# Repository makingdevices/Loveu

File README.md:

<!-- Improved compatibility of back to top link: See: https://github.com/othneildrew/Best-README-Template/pull/73 -->

<!--
*** Thanks for checking out the Best-README-Template. If you have a suggestion
*** that would make this better, please fork the repo and create a pull request
*** or simply open an issue with the tag "enhancement".
*** Don't forget to give the project a star!
*** Thanks again! Now go create something AMAZING! :D
-->

<!-- PROJECT SHIELDS -->
<!--
*** I'm using markdown "reference style" links for readability.
*** Reference links are enclosed in brackets [ ] instead of parentheses ( ).
*** See the bottom of this document for the declaration of the reference variables
*** for contributors-url, forks-url, etc. This is an optional, concise syntax you may use.
*** https://www.markdownguide.org/basic-syntax/#reference-style-links
-->
[![Instagram][ig-shield]][ig-url]
[![PCBWAY][sponsor-shield]][sponsor-url]
[![Stargazers][stars-shield]][stars-url]
[![Issues][issues-shield]][issues-url]
[![LinkedIn][linkedin-shield]][linkedin-url]

<!-- PROJECT LOGO -->
<br />
<div align="center">

<h3 align="center">Making Devices</h3>

  <p align="center">
    Open Source projects where we struggle with engineering, electronics, coding and who knows what else... In this case, Loveu is a heart-shaped PCB for saint Valentine
  </p>
</div>

<!-- TABLE OF CONTENTS -->
<details>
  <summary>Table of Contents</summary>
  <ol>
    <li>
      <a href="#about-the-project">About The Project</a>
      <ul>
        <li><a href="#built-with">Built With</a></li>
      </ul>
    </li>
    <li>
      <a href="#Build-one">Build one</a>
      <ul>
      </ul>
    </li>
    <li><a href="#usage">Usage</a></li>
    <li><a href="#roadmap">Roadmap</a></li>
    <li><a href="#license">License</a></li>
    <li><a href="#contact">Contact</a></li>
    <li><a href="#Sponsor">Sponsor</a></li>
  </ol>
</details>

<!-- ABOUT THE PROJECT -->
## About The Project

[![Bytes Counter Shot][product-screenshot]](https://github.com/makingdevices/Loveu)

Heart shaped PCB that was intended to blink with the harvested power of the micro solar panels. Unfortunately, it did not work. 

This device is under development, so I do encourage you to not assembly, order any PCB or use any software from this repository until the project is finished.

<p align="right">(<a href="#readme-top">back to top</a>)</p>

### Built With

[![Kicad][kicad-shield]][kicad-url]
[![SPONSOR][sponsor-icon]][sponsor-url]

<p align="right">(<a href="#readme-top">back to top</a>)</p>

<!-- GETTING STARTED -->

## Build one
NOT RECOMMENDED AS THE DEVICE IS UNDER DEVELOPMENT

<p align="right">(<a href="#readme-top">back to top</a>)</p>

<!-- USAGE EXAMPLES -->
## Usage

Instructions of use:

- The heart blinks with the sun

<p align="right">(<a href="#readme-top">back to top</a>)</p>

<!-- ROADMAP -->
## Roadmap

- [ ] Re Design

See the [open issues](https://github.com/makingdevices/Loveu/issues) for a full list of proposed features (and known issues).

State: Project <b>UNFINISHED</b> - 08/01/2023

Priority: <b>None</b>

<p align="right">(<a href="#readme-top">back to top</a>)</p>

<!-- LICENSE -->
## License

Distributed under three licenses:
- [Hardware](/License/HW_cern_ohl_s_v2.pdf)
- [Software](/License/SW_GPLv3.0.txt)
- [Documentation](/License/Documentation_CC-BY-SA-4.0.txt)

[![GPL v3 License][license-shield]][license-url] 
<p align="right">(<a href="#readme-top">back to top</a>)</p>

<!-- CONTACT -->
## Contact

Making Devices - [@MakingDevices](https://www.instagram.com/makingdevices/)

Project Link: [https://github.com/makingdevices/Loveu](https://github.com/makingdevices/Loveu/)

Other Links: [LinkTree](https://makingdevices.com/links/)

<p align="right">(<a href="#readme-top">back to top</a>)</p>

<!-- MARKDOWN LINKS & IMAGES -->
<!-- https://www.markdownguide.org/basic-syntax/#reference-style-links -->
[contributors-shield]: https://img.shields.io/github/contributors/makingdevices/Loveu.svg?style=for-the-badge
[contributors-url]: https://github.com/makingdevices/Loveu/graphs/contributors
[forks-shield]: https://img.shields.io/github/forks/makingdevices/Loveu.svg?style=for-the-badge
[forks-url]: https://github.com/makingdevices/Loveu/network/members
[stars-shield]: https://img.shields.io/github/stars/makingdevices/Loveu.svg?style=for-the-badge
[stars-url]: https://github.com/makingdevices/Loveu/stargazers
[issues-shield]: https://img.shields.io/github/issues/makingdevices/Loveu.svg?style=for-the-badge
[issues-url]: https://github.com/makingdevices/Loveu/issues
[license-shield]: /images/license.png
[license-url]: https://github.com/makingdevices/Loveu/tree/main/License
[linkedin-shield]: https://img.shields.io/badge/-LinkedIn-black.svg?style=for-the-badge&logo=linkedin&colorB=555
[linkedin-url]: https://www.linkedin.com/company/making-devices/
[sponsor-shield]: https://img.shields.io/badge/SPONSOR-PCBWAY-black.svg?style=for-the-badge&colorB=1200
[sponsor-url]: https://www.pcbway.com/?from=makingdevices
[sponsor-screenshot]: /images/PCB_sponsor.png
[product-screenshot]: images/screenshot.jpg
[PIC]: https://img.shields.io/badge/PIC18LF45K50-000000?style=for-the-badge
[PIC-url]: http://ww1.microchip.com/downloads/en/devicedoc/40001350f.pdf
[kicad-shield]: https://img.shields.io/badge/kicad-0b03fc?style=for-the-badge&logo=kicad&logoColor=white
[kicad-url]: https://www.kicad.org/
[YT-screenshot]: images/YT_assembly.PNG
[sponsor-icon]:  https://img.shields.io/badge/-PCBWAY-black.svg?style=for-the-badge&colorB=1200
[ig-shield]: https://img.shields.io/badge/instagram-a83297?style=for-the-badge&logo=instagram&logoColor=white
[ig-url]: https://www.instagram.com/makingdevices/
[MPLAB-C]: https://img.shields.io/badge/MPLAB%20C18-DD0031?style=for-the-badge&logo=C&logoColor=white
[MPLAB-C-url]: https://www.microchip.com/en-us/development-tool/SW006011
[Svelte.dev]: https://img.shields.io/badge/Svelte-4A4A55?style=for-the-badge&logo=svelte&logoColor=FF3E00
[Svelte-url]: https://svelte.dev/
[Laravel.com]: https://img.shields.io/badge/Laravel-FF2D20?style=for-the-badge&logo=laravel&logoColor=white
[Laravel-url]: https://laravel.com
[Bootstrap.com]: https://img.shields.io/badge/Bootstrap-563D7C?style=for-the-badge&logo=bootstrap&logoColor=white
[Bootstrap-url]: https://getbootstrap.com
[JQuery.com]: https://img.shields.io/badge/jQuery-0769AD?style=for-the-badge&logo=jquery&logoColor=white
[JQuery-url]: https://jquery.com

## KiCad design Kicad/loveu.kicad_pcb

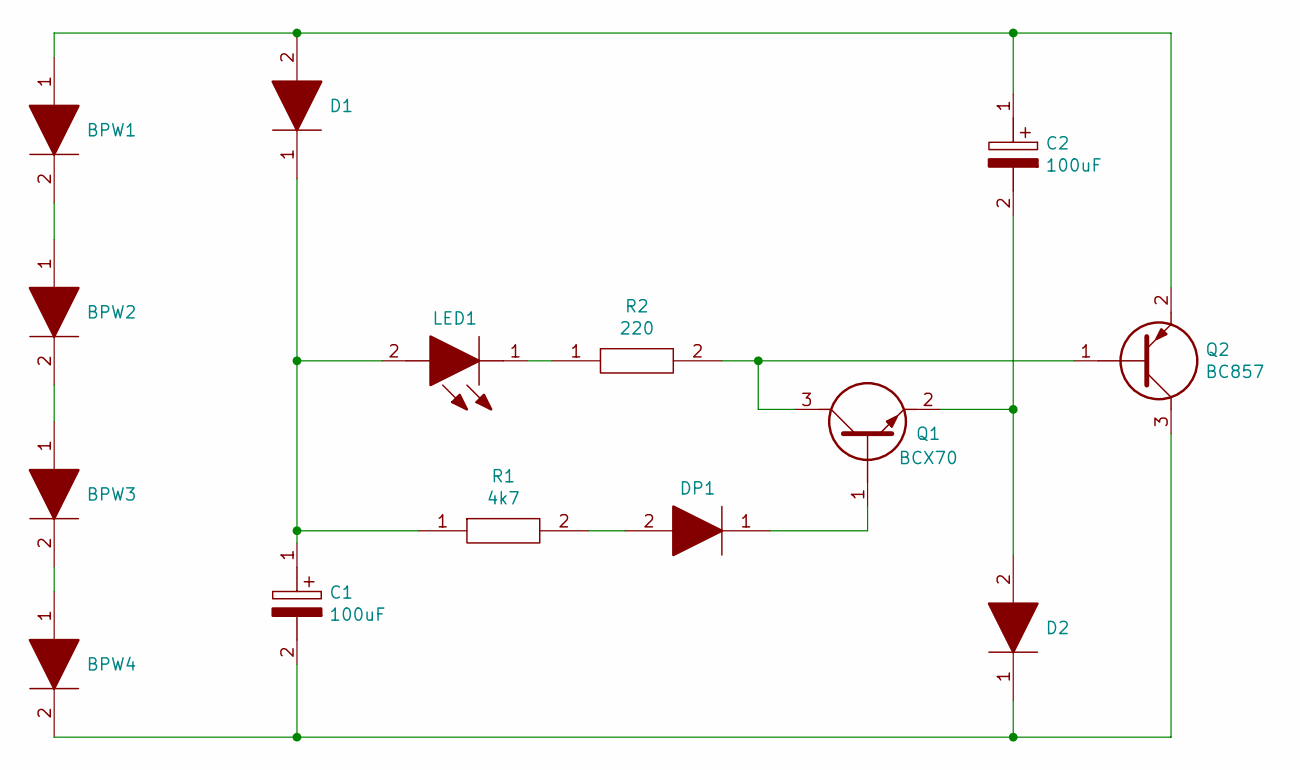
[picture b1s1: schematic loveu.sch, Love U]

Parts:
BPW1, BPW2, BPW3, BPW4: BPW_34_SR-Z; BPW34SRZ; Mouser Part Number 720-BPW34SR-Z
C1, C2: 100uF; CAPPM6032X280N; Mouser Part Number 581-TCJC107M06R100E
D1, D2: ZLLS410TA; SOD2513X120N; Manufacturer_Part_Number ZLLS410TA
DP1: BAV21WS_R1_00001; SODFL2512X90N; Mouser Part Number 241-BAV21WS_R1_00001
LED1: SML-H12V8TT86; LEDC2012X90N; Manufacturer_Part_Number SML-H12V8TT86
Q1: BCX70; SOT95P230X110-3N; Mouser Part Number 771-BCX70J235
Q2: BC857; SOT95P230X110-3N; Mouser Part Number 771-BC858B235
R1: 4k7; RESC2012X75N; Manufacturer_Part_Number ERJP6WF1303V
R2: 220; RESC2012X75N; Manufacturer_Part_Number ERJP6WF1303V

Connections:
unnamed: BPW1.1, C2.1, D1.2, Q2.2
unnamed: BPW1.2, BPW2.1
unnamed: BPW2.2, BPW3.1
unnamed: BPW3.2, BPW4.1
unnamed: BPW4.2, C1.2, D2.1, Q2.3
unnamed: C1.1, D1.1, LED1.2, R1.1
unnamed: C2.2, D2.2, Q1.2
unnamed: DP1.1, Q1.1
unnamed: DP1.2, R1.2
unnamed: LED1.1, R2.1
unnamed: Q1.3, Q2.1, R2.2

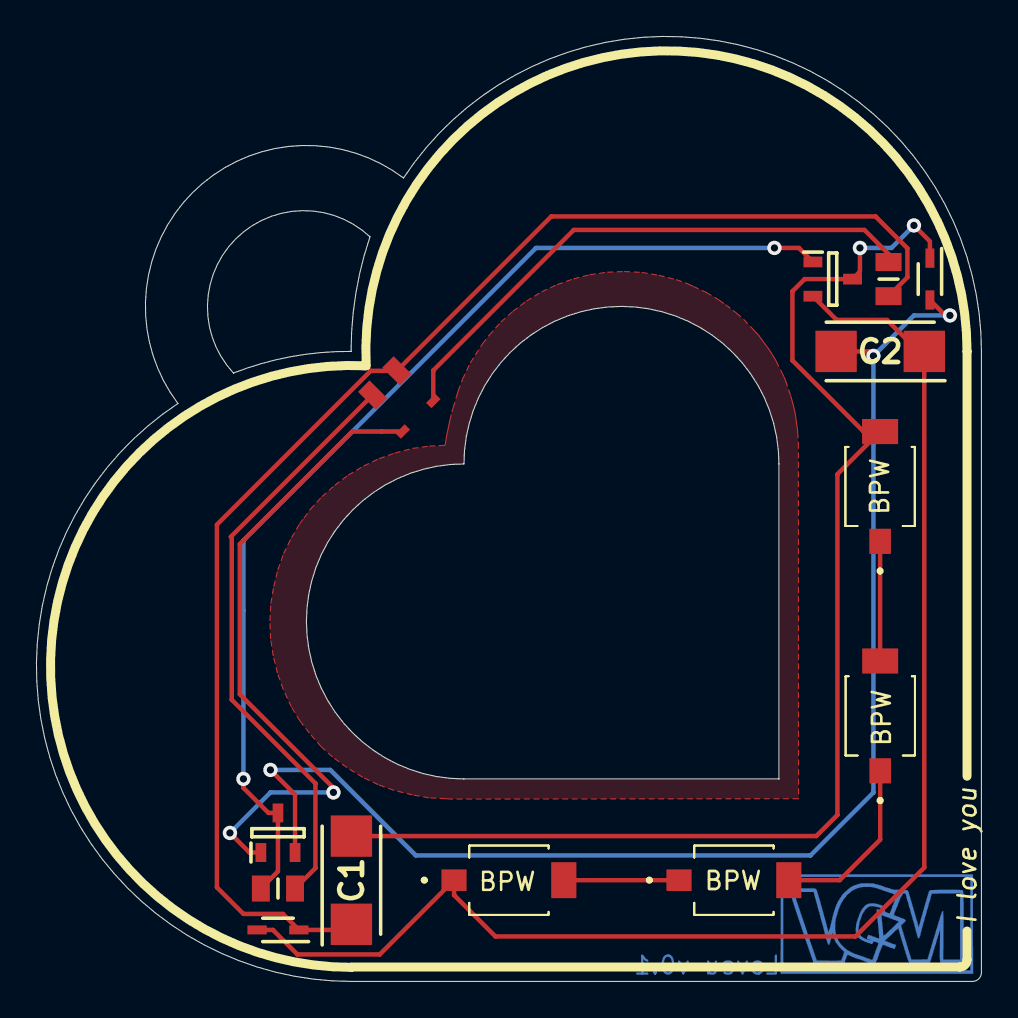
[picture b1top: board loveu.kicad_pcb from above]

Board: 2 copper layers, 52.5 x 52.5 mm, 14 parts (0 on the bottom side), 11 nets.

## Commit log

2023-01-08 Update files
2023-01-08 no message
